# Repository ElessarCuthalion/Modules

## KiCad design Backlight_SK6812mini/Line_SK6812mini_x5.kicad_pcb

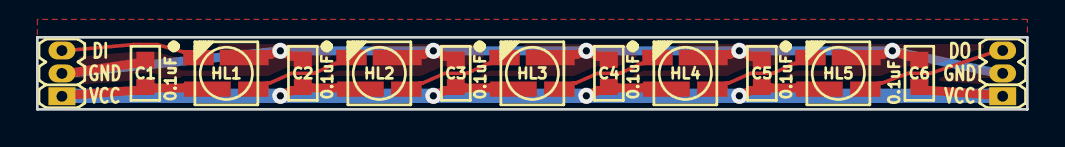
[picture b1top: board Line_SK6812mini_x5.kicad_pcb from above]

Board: 2 copper layers, 55.0 x 4.0 mm, 14 parts (1 on the bottom side), 8 nets.

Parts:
C1, C2, C3, C4, C5, C6: 0.1uF; CAP0603
HL1, HL2, HL3, HL4, HL5: SK6812mini
Logo1: Eldalim; Eldalim_5x4_back
XP1: Input; for_WS2812_PLL1.27-3
XP2: Output; for_WS2812_PLL1.27-3

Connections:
/VDD: C1.1, C2.1, C3.1, C4.1, C5.1, C6.1, HL1.4, HL2.4, HL3.4, HL4.4, HL5.4, XP1.1, XP2.1
GND: C1.2, C2.2, C3.2, C4.2, C5.2, C6.2, HL1.2, HL2.2, HL3.2, HL4.2, HL5.2, XP1.2, XP2.2
unnamed: HL1.1, HL2.3
unnamed: HL1.3, XP1.3
unnamed: HL2.1, HL3.3
unnamed: HL3.1, HL4.3
unnamed: HL4.1, HL5.3
unnamed: HL5.1, XP2.3

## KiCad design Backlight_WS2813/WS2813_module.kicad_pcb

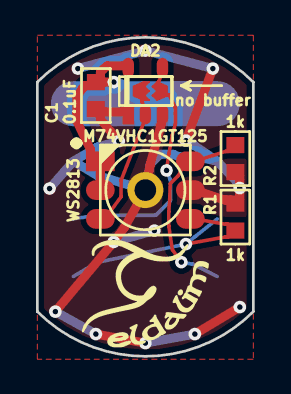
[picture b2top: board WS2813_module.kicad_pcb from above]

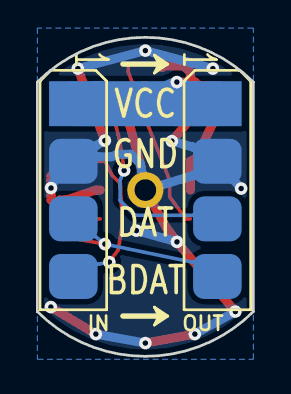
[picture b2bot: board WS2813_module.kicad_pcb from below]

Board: 2 copper layers, 12.0 x 17.7 mm, 10 parts (2 on the bottom side), 6 nets.

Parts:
C1: 0.1uF; CAP0603
DA2: M74VHC1GT125; SOT23-5
HL1: WS2813
Hole1: HoleMetalled; Hole_for_M2
Logo1: Eldalim; Eldalim_7x6
R1, R2: 1k; RES0603
XP1: IN; for_WS2813_AVX_00-9176
XP2: OUT; for_WS2813_AVX_00-9176
fus1: no buffer; FuseSolder

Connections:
+VCC: C1.1, DA2.5, HL1.1, HL1.2, XP1.1, XP2.1
/BDin: HL1.6, R2.1, XP1.4
/Din: HL1.4, R1.1, XP1.3, XP2.4
/Dout: DA2.4, XP2.3, fus1.2
GND: C1.2, DA2.1, DA2.3, HL1.5, Hole1.H, R1.2, R2.2, XP1.2, XP2.2
unnamed: DA2.2, HL1.3, fus1.1

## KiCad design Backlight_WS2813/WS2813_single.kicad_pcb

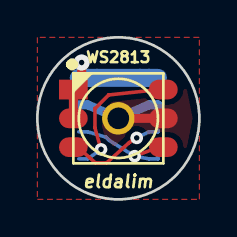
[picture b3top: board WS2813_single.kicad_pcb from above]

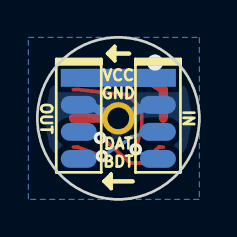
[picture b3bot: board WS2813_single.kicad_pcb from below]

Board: 2 copper layers, 9.0 x 9.0 mm, 4 parts (2 on the bottom side), 5 nets.

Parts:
HL1: WS2813
Hole1: HoleMetalled; Hole_for_M2
XP1: IN; FlatConn-4_1,5
XP2: OUT; FlatConn-4_1,5

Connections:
+VCC: HL1.1, HL1.2, XP1.1, XP2.1
/BDin: HL1.6, XP1.4
/Din: HL1.4, XP1.3, XP2.4
/Dout: HL1.3, XP2.3
GND: HL1.5, Hole1.H, XP1.2, XP2.2
